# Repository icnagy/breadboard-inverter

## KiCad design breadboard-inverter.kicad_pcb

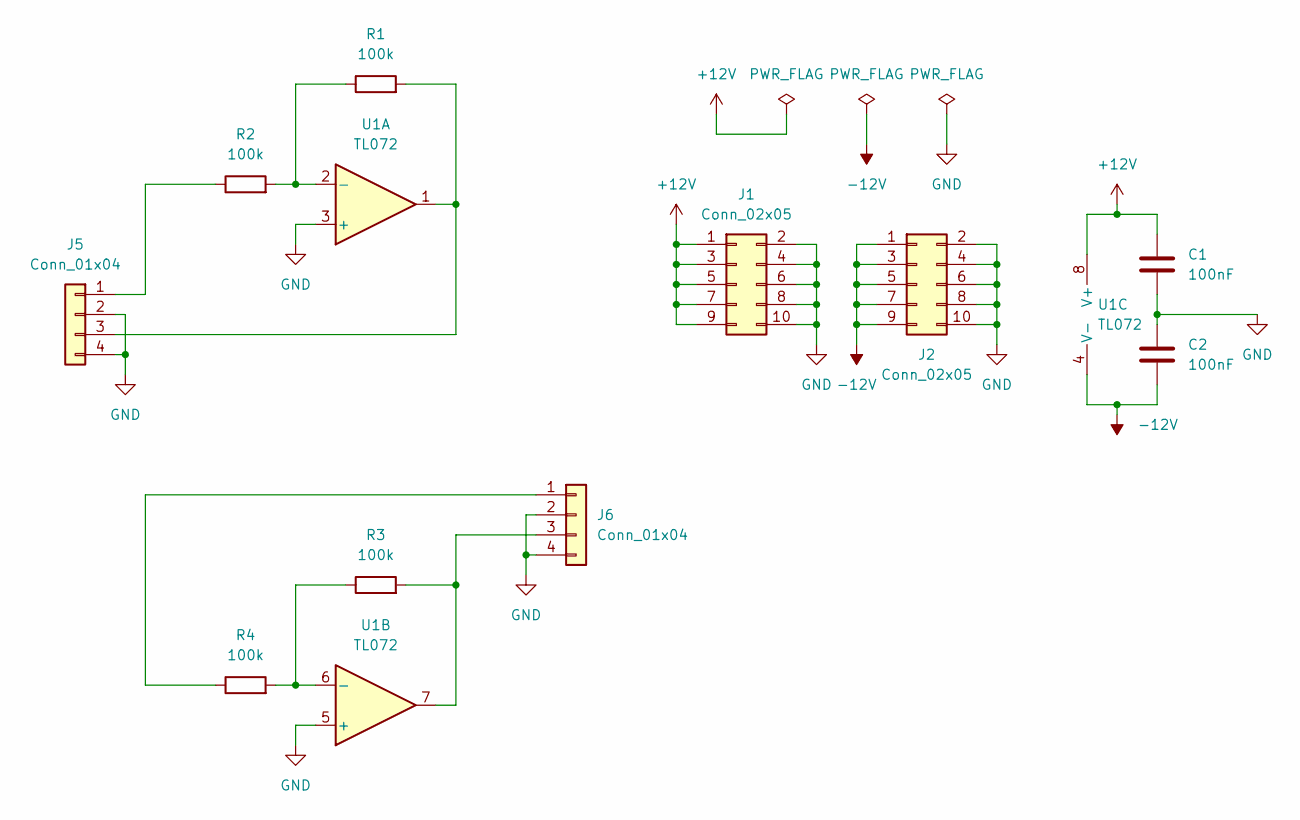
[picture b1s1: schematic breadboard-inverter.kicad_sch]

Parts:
C1, C2: 100nF; C_Disc_D4.7mm_W2.5mm_P5.00mm
J1, J2: Conn_02x05; PinHeader_2x05_P2.54mm_Vertical
J5, J6: Conn_01x04; PinHeader_1x04_P2.54mm_Vertical
R1, R2, R3, R4: 100k; R_Axial_DIN0207_L6.3mm_D2.5mm_P2.54mm_Vertical
U1: TL072; DIP-8_W7.62mm_Socket

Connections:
+12V: C1.1, J1.1, J1.3, J1.5, J1.7, J1.9, U1.8 (V+)
-12V: C2.2, J2.1, J2.3, J2.5, J2.7, J2.9, U1.4 (V-)
GND: C1.2, C2.1, J1.2, J1.4, J1.6, J1.8, J1.10, J2.2, J2.4, J2.6, J2.8, J2.10, J5.2, J5.4, J6.2, J6.4, U1.3 (+), U1.5 (+)
unnamed: J5.1, R2.1
unnamed: J5.3, R1.2, U1.1
unnamed: J6.1, R4.1
unnamed: J6.3, R3.2, U1.7
unnamed: R1.1, R2.2, U1.2 (-)
unnamed: R3.1, R4.2, U1.6 (-)

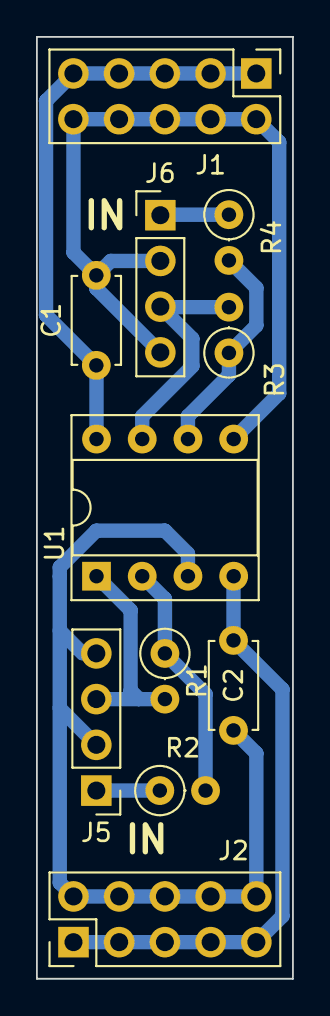
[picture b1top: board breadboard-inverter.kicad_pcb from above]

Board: 2 copper layers, 14.2 x 52.3 mm, 11 parts (0 on the bottom side), 9 nets.

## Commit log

2022-06-10 Add image and schematic
2022-06-10 Add readme
2023-05-29 Kicad 7.0.5 upgrade
